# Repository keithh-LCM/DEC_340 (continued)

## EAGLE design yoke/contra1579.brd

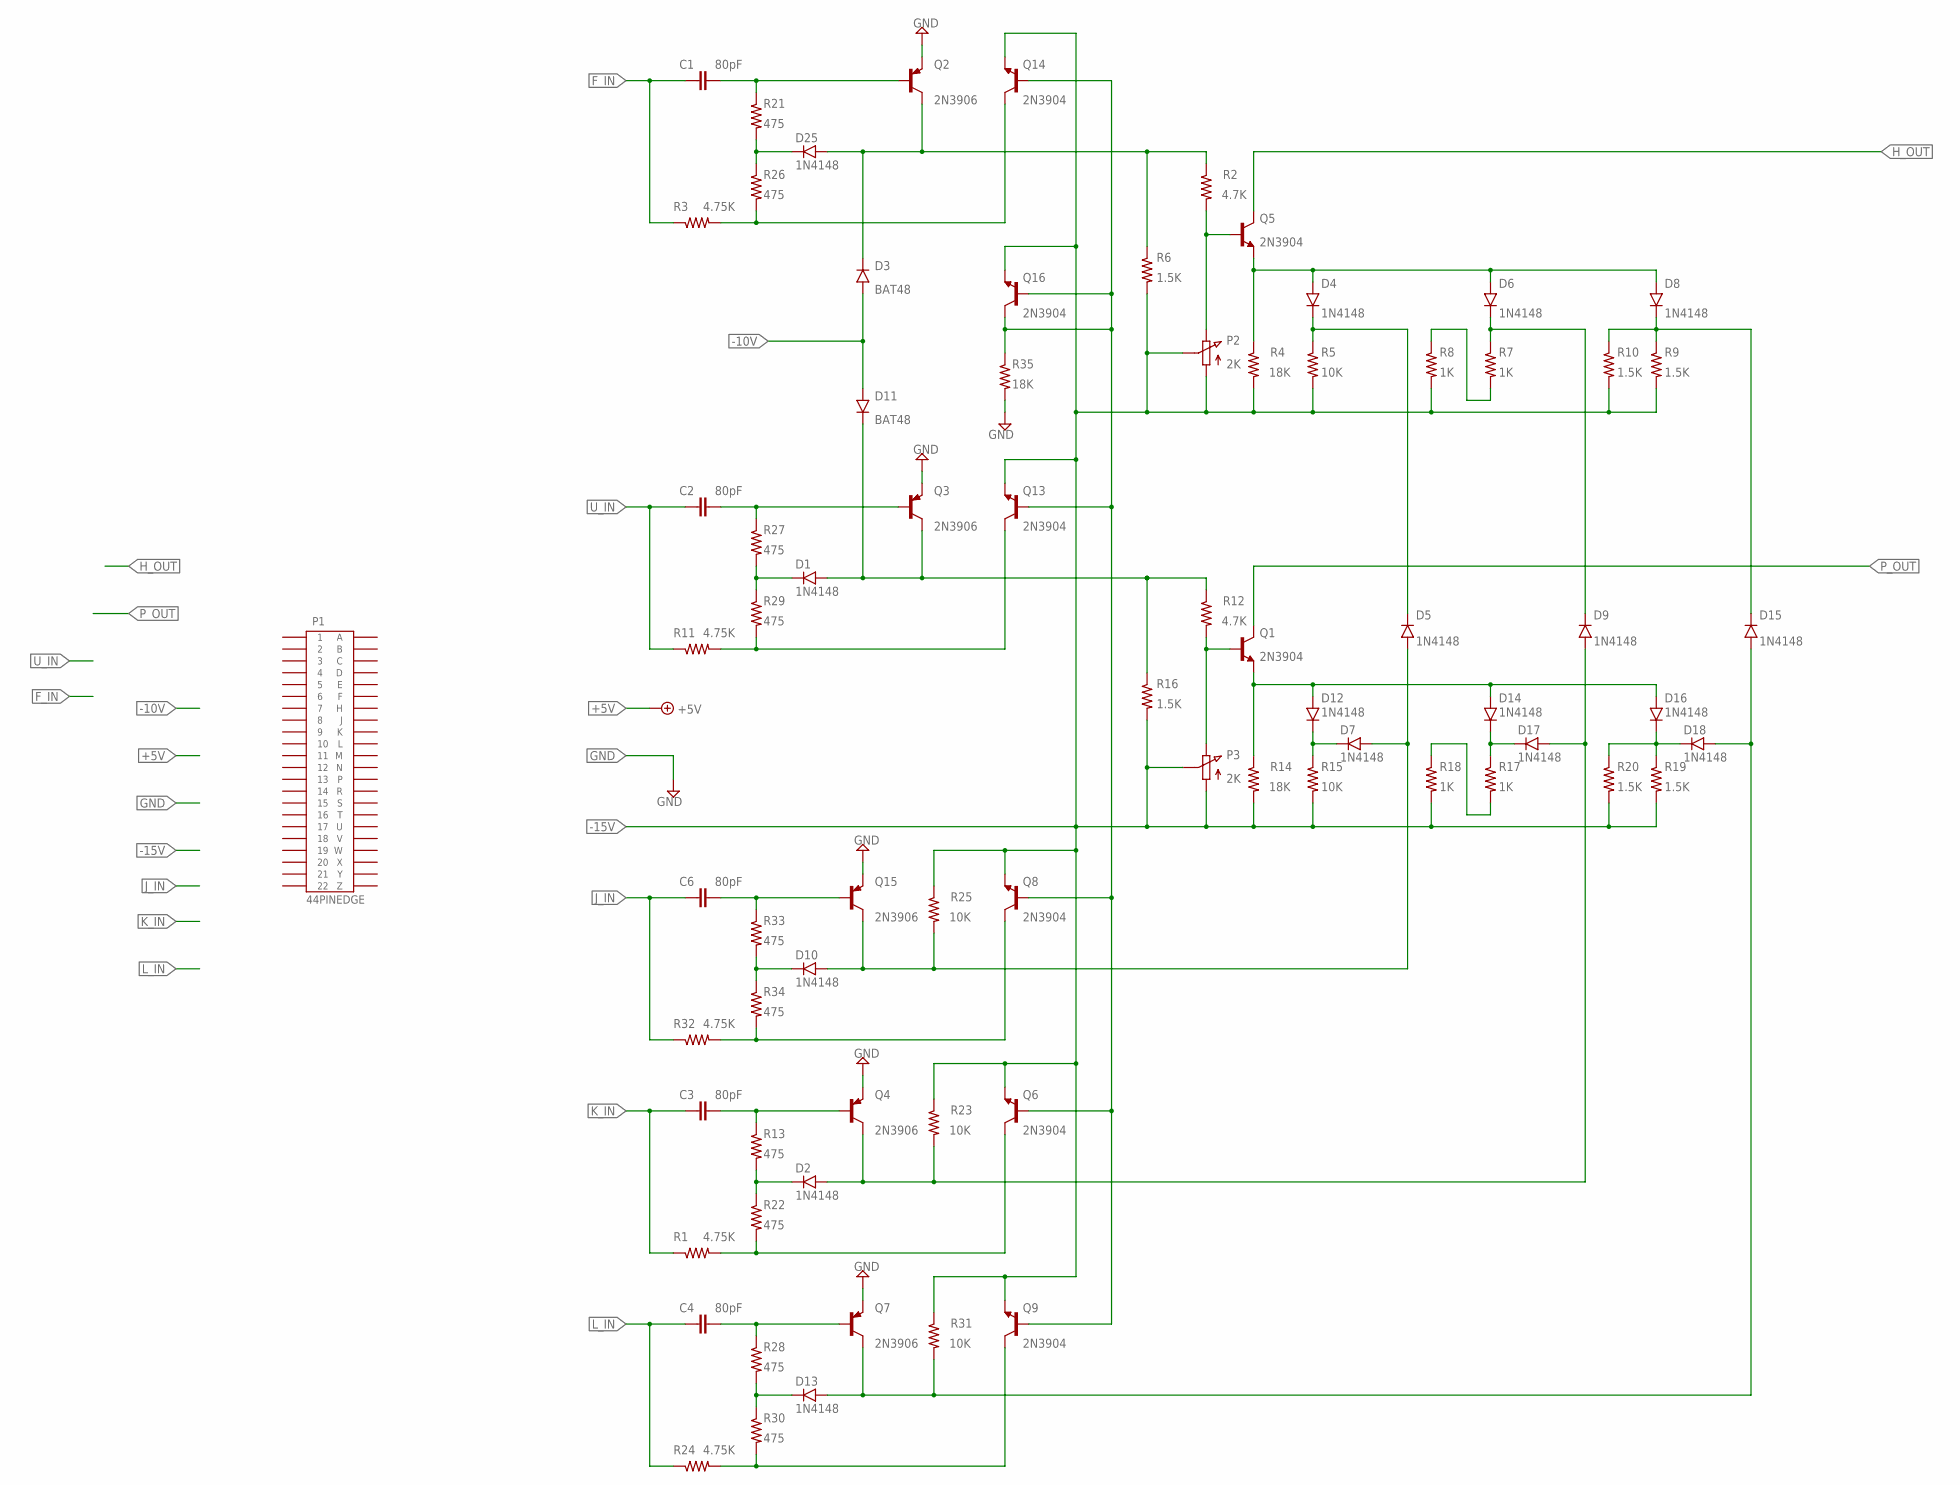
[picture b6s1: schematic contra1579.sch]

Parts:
C1, C2, C3, C4, C6: 80pF; 5MM_TH
D1, D2, D4, D5, D6, D7, D8, D9, D10, D12, D13, D14, D15, D16, D17, D18, D25: 1N4148; DO35-7
D3, D11: BAT48; DO35-7
P1: 44PINEDGE
P2, P3: 2K; 3006P
Q1, Q5, Q6, Q8, Q9, Q13, Q14, Q16: 2N3904; TO92
Q2, Q3, Q4, Q7, Q15: 2N3906; TO92
R1, R3, R11, R24, R32: 4.75K; 0207/10
R2, R12: 4.7K; 0207/10
R4, R14, R35: 18K; 0207/10
R5, R15, R23, R25, R31: 10K; 0207/10
R6, R9, R10, R16, R19, R20: 1.5K; 0207/10
R7, R8, R17, R18: 1K; 0207/10
R13, R21, R22, R26, R27, R28, R29, R30, R33, R34: 475; 0207/10

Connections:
-10V: D3.A, D11.A
-15V: P2.1 (A), P2.2 (S), P3.1 (A), P3.2 (S), Q6.3 (E), Q8.3 (E), Q9.3 (E), Q13.3 (E), Q14.3 (E), Q16.3 (E), R4.2, R5.2, R6.2, R8.2, R9.2, R10.2, R14.2, R15.2, R16.2, R18.2, R19.2, R20.2, R23.1, R25.1, R31.1
F_IN: C1.1, R3.1
GND: Q2.3 (E), Q3.3 (E), Q4.3 (E), Q7.3 (E), Q15.3 (E), R35.2
H_OUT: Q5.1 (C)
J_IN: C6.1, R32.1
K_IN: C3.1, R1.1
L_IN: C4.1, R24.1
unnamed: C1.2, Q2.2 (B), R21.1
unnamed: Q14.1 (C), R3.2, R26.2
unnamed: C3.2, Q4.2 (B), R13.1
unnamed: P2.3 (E), Q5.2 (B), R2.2
unnamed: D4.A, D6.A, D8.A, Q5.3 (E), R4.1
unnamed: D4.C, D5.C, R5.1
unnamed: R7.2, R8.1
unnamed: Q6.1 (C), R1.2, R22.2
unnamed: D25.C, R21.2, R26.1
unnamed: D6.C, D9.C, R7.1
unnamed: D8.C, D15.C, R9.1, R10.1
unnamed: D2.C, R13.2, R22.1
unnamed: C4.2, Q7.2 (B), R28.1
unnamed: C2.2, Q3.2 (B), R27.1
unnamed: Q13.1 (C), R11.2, R29.2
unnamed: P3.3 (E), Q1.2 (B), R12.2
unnamed: D12.A, D14.A, D16.A, Q1.3 (E), R14.1
unnamed: D7.C, D12.C, R15.1
unnamed: D14.C, D17.C, R17.1
unnamed: R17.2, R18.1
unnamed: D16.C, D18.C, R19.1, R20.1
unnamed: Q9.1 (C), R24.2, R30.2
unnamed: D13.C, R28.2, R30.1
unnamed: D1.C, R27.2, R29.1
unnamed: C6.2, Q15.2 (B), R33.1
unnamed: Q8.1 (C), R32.2, R34.2
unnamed: D10.C, R33.2, R34.1
unnamed: Q6.2 (B), Q8.2 (B), Q9.2 (B), Q13.2 (B), Q14.2 (B), Q16.1 (C), Q16.2 (B), R35.1
P_OUT: Q1.1 (C)
U_IN: C2.1, R11.1
VREF: D3.C, D25.A, Q2.1 (C), R2.1, R6.1
VREF1: D2.A, D9.A, D17.A, Q4.1 (C), R23.2
VREF2: D13.A, D15.A, D18.A, Q7.1 (C), R31.2
VREF3: D5.A, D7.A, D10.A, Q15.1 (C), R25.2
VREF5: D1.A, D11.C, Q3.1 (C), R12.1, R16.1

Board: 2 copper layers, 75 parts (0 on the bottom side), 41 nets, no tracks yet.

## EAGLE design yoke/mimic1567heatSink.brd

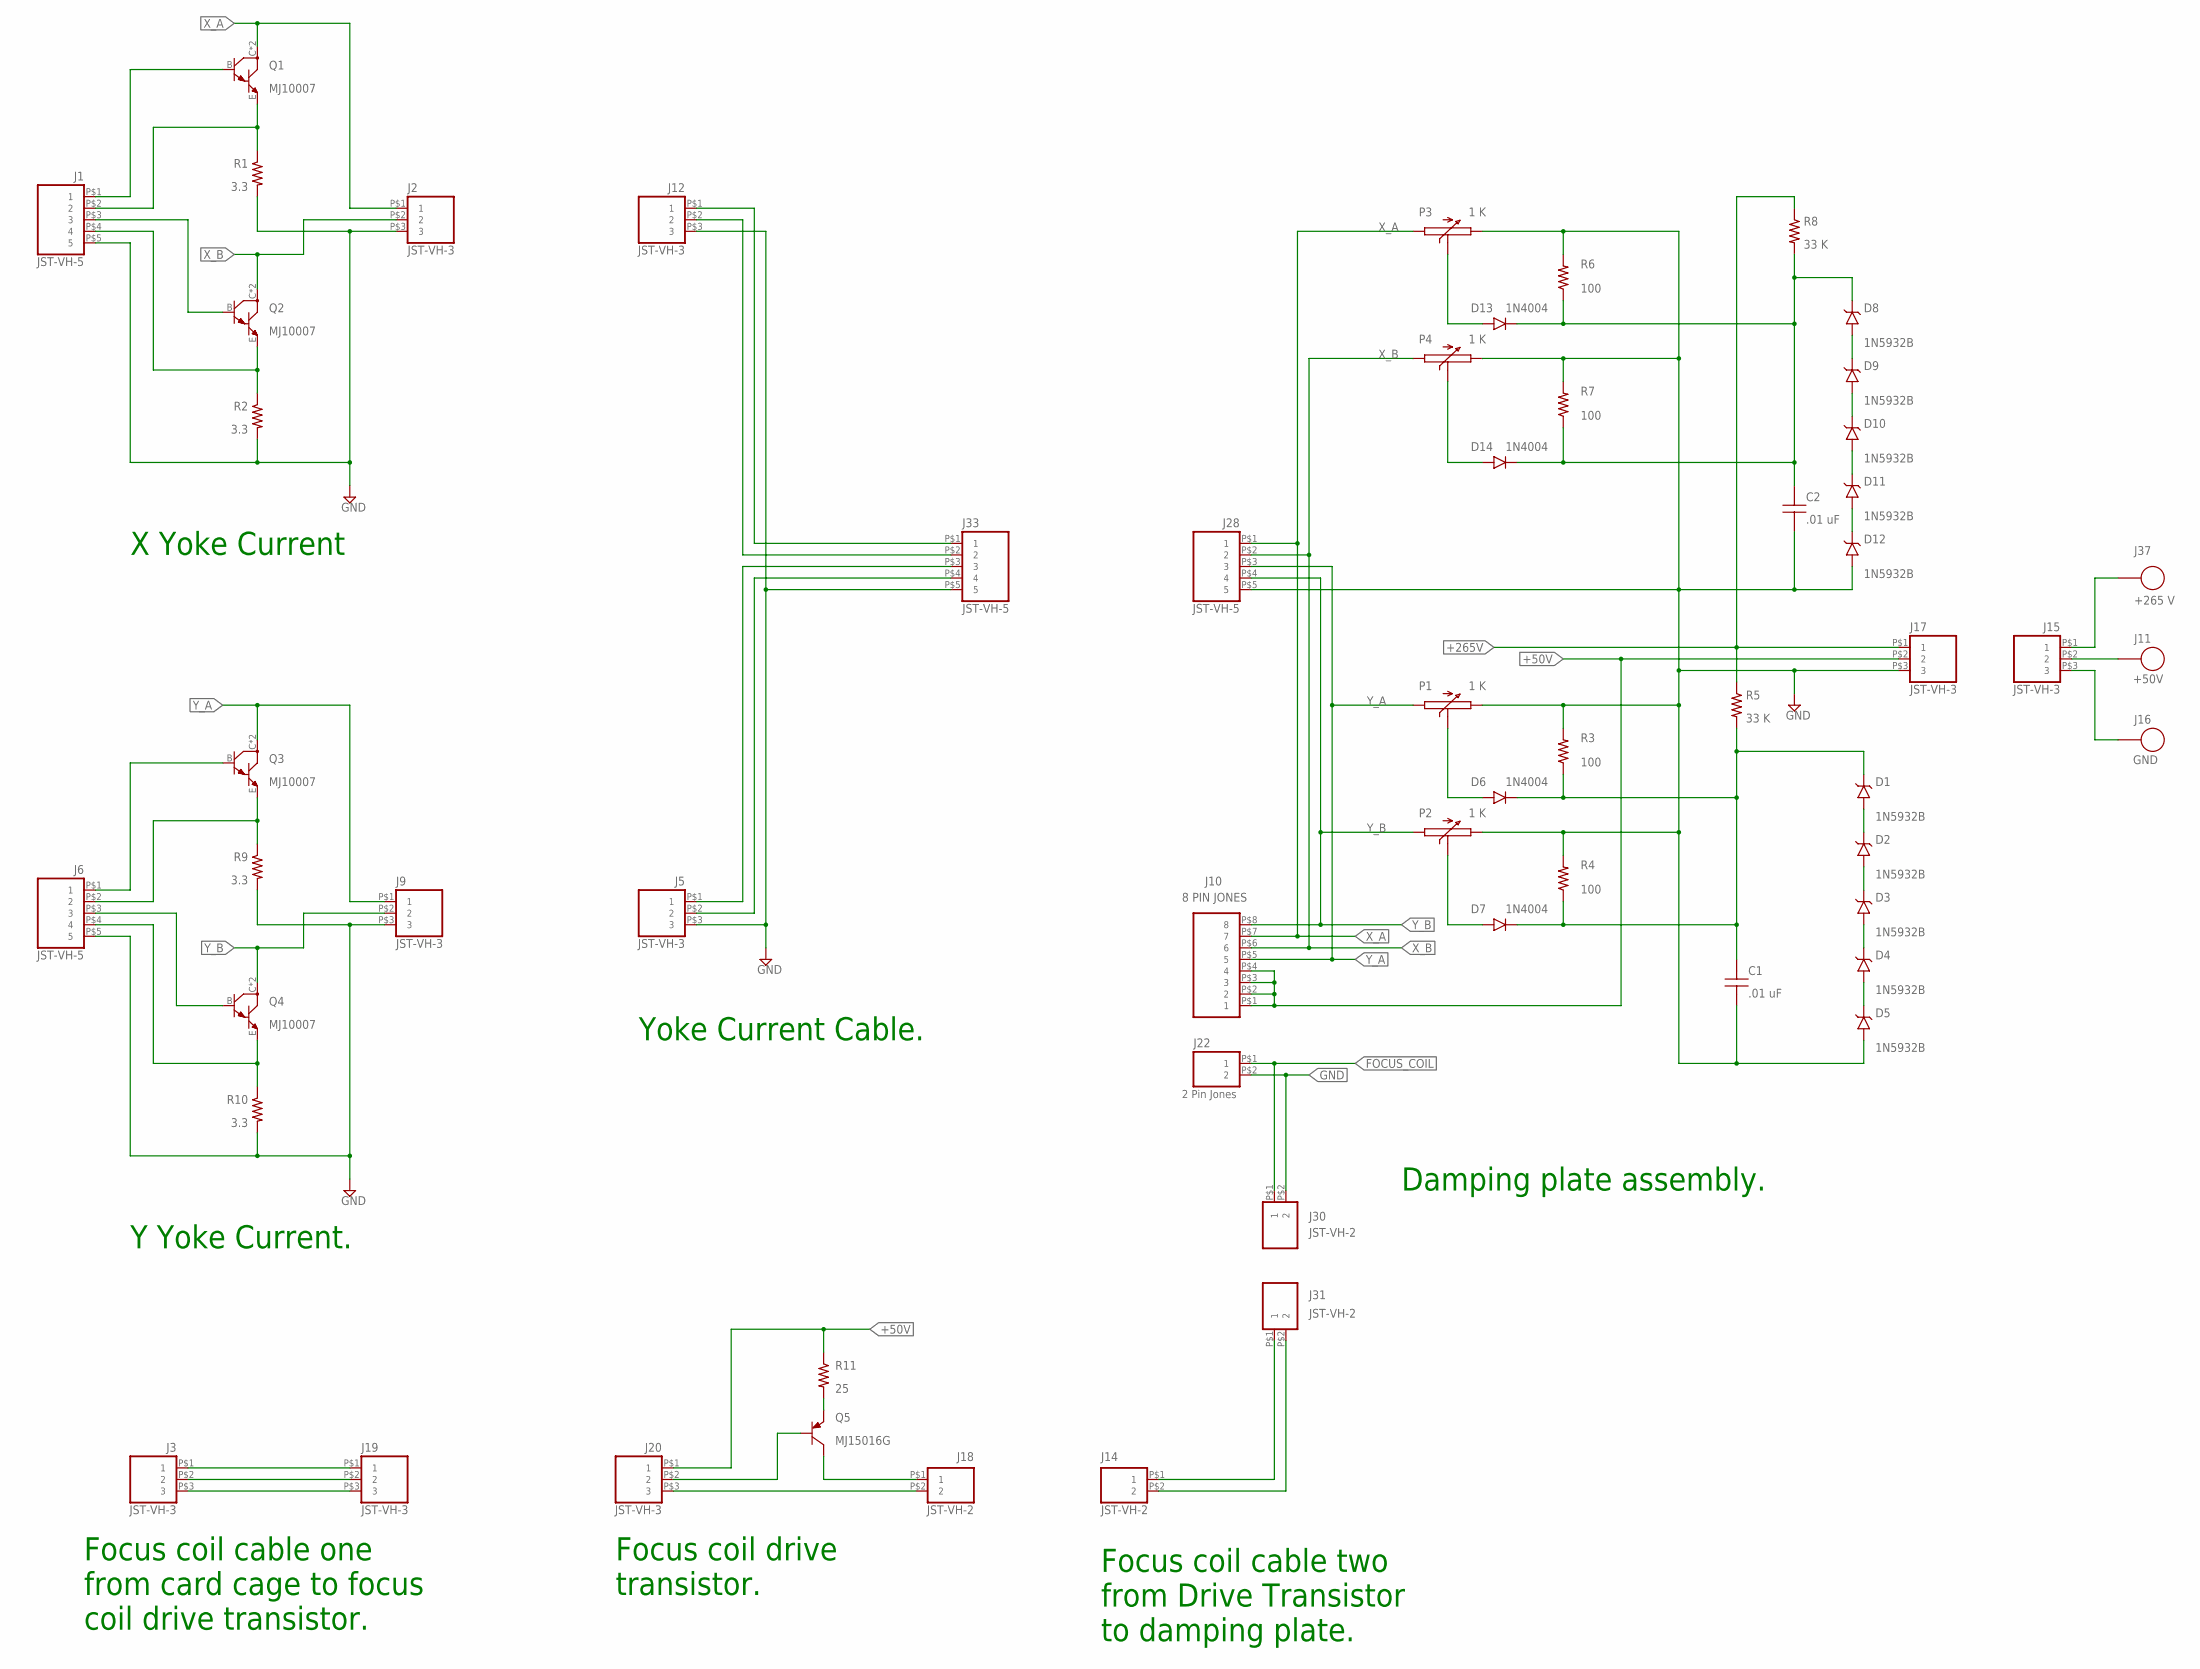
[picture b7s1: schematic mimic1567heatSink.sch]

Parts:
C1, C2: .01 uF; CAP/RADIAL/15MM
D1, D2, D3, D4, D5, D8, D9, D10, D11, D12: 1N5932B; DO41
D6, D7, D13, D14: 1N4004; DO-41-10
J1, J6, J28, J33: JST-VH-5; VHR-5N
J2, J3, J5, J9, J12, J15, J17, J19, J20: JST-VH-3; VHR-3N
J10: 8 PIN JONES; 8PIN_JONES
J11: +50V; AWG18
J14, J18, J30, J31: JST-VH-2; VHR-2N
J16: GND; AWG18
J22: 2 Pin Jones; 2PIN_JONES
J37: +265 V; AWG18
P1, P2, P3, P4: 1 K; 2W_POT
Q1, Q2, Q3, Q4: MJ10007; TO3
Q5: MJ15016G; TO3
R1, R2, R9, R10: 3.3; R_150WATT
R3, R4, R6, R7: 100; 0309/12
R5, R8: 33 K; 2WATT/15
R11: 25; DALE-RH

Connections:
+50V: J10.P$1 (1), J10.P$2 (2), J10.P$3 (3), J10.P$4 (4), J17.P$2 (2), J20.P$1 (1), R11.1
+265V: J17.P$1 (1), R5.1, R8.1
FOCUS_COIL: J18.P$1 (1), J22.P$1 (1), J30.P$1 (1), Q5.C, Q5.C/ (C)
GND: C1.P$2 (2), C2.P$2 (2), D5.A, D12.A, J1.P$5 (5), J2.P$3 (3), J5.P$3 (3), J6.P$5 (5), J9.P$3 (3), J12.P$3 (3), J17.P$3 (3), J18.P$2 (2), J20.P$3 (3), J22.P$2 (2), J28.P$5 (5), J30.P$2 (2), J33.P$5 (5), P1.E (3), P2.E (3), P3.E (3), P4.E (3), R1.P$2, R2.P$2, R3.2, R4.2, R6.2, R7.2, R9.P$2, R10.P$2
unnamed: J20.P$2 (2), Q5.B
unnamed: J1.P$1 (1), Q1.B
unnamed: J1.P$2 (2), Q1.E, R1.P$1
unnamed: Q5.E, R11.2
unnamed: J1.P$4 (4), Q2.E, R2.P$1
unnamed: J1.P$3 (3), Q2.B
unnamed: J3.P$3 (3), J19.P$3 (3)
unnamed: J3.P$2 (2), J19.P$2 (2)
unnamed: D1.A, D2.C
unnamed: D2.A, D3.C
unnamed: D3.A, D4.C
unnamed: D4.A, D5.C
unnamed: J15.P$1 (1), J37.P$1
unnamed: C1.P$1 (1), D1.C, D6.C, D7.C, R3.1, R4.1, R5.2
unnamed: D6.A, P1.S (2)
unnamed: J11.P$1, J15.P$2 (2)
unnamed: J15.P$3 (3), J16.P$1
unnamed: D8.A, D9.C
unnamed: D7.A, P2.S (2)
unnamed: J6.P$3 (3), Q4.B
unnamed: D9.A, D10.C
unnamed: D10.A, D11.C
unnamed: D11.A, D12.C
unnamed: J14.P$2 (2), J31.P$2 (2)
unnamed: J3.P$1 (1), J19.P$1 (1)
unnamed: J6.P$1 (1), Q3.B
unnamed: C2.P$1 (1), D8.C, D13.C, D14.C, R6.1, R7.1, R8.2
unnamed: J6.P$2 (2), Q3.E, R9.P$1
unnamed: D13.A, P3.S (2)
unnamed: J14.P$1 (1), J31.P$1 (1)
unnamed: D14.A, P4.S (2)
unnamed: J6.P$4 (4), Q4.E, R10.P$1
X_A: J2.P$1 (1), J10.P$7 (7), J12.P$1 (1), J28.P$1 (1), J33.P$1 (1), P3.A (1), Q1.C, Q1.C/ (C)
X_B: J2.P$2 (2), J10.P$6 (6), J12.P$2 (2), J28.P$2 (2), J33.P$2 (2), P4.A (1), Q2.C, Q2.C/ (C)
Y_A: J5.P$1 (1), J9.P$1 (1), J10.P$5 (5), J28.P$3 (3), J33.P$3 (3), P1.A (1), Q3.C, Q3.C/ (C)
Y_B: J5.P$2 (2), J9.P$2 (2), J10.P$8 (8), J28.P$4 (4), J33.P$4 (4), P2.A (1), Q4.C, Q4.C/ (C)

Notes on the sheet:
Damping plate assembly.
Focus coil cable two from Drive Transistor to damping plate.
Yoke Current Cable.
Focus coil cable one from card cage to focus coil drive transistor.
Focus coil drive transistor.
X Yoke Current
Y Yoke Current.

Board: 2 copper layers, 58 parts (0 on the bottom side), 40 nets, no tracks yet.

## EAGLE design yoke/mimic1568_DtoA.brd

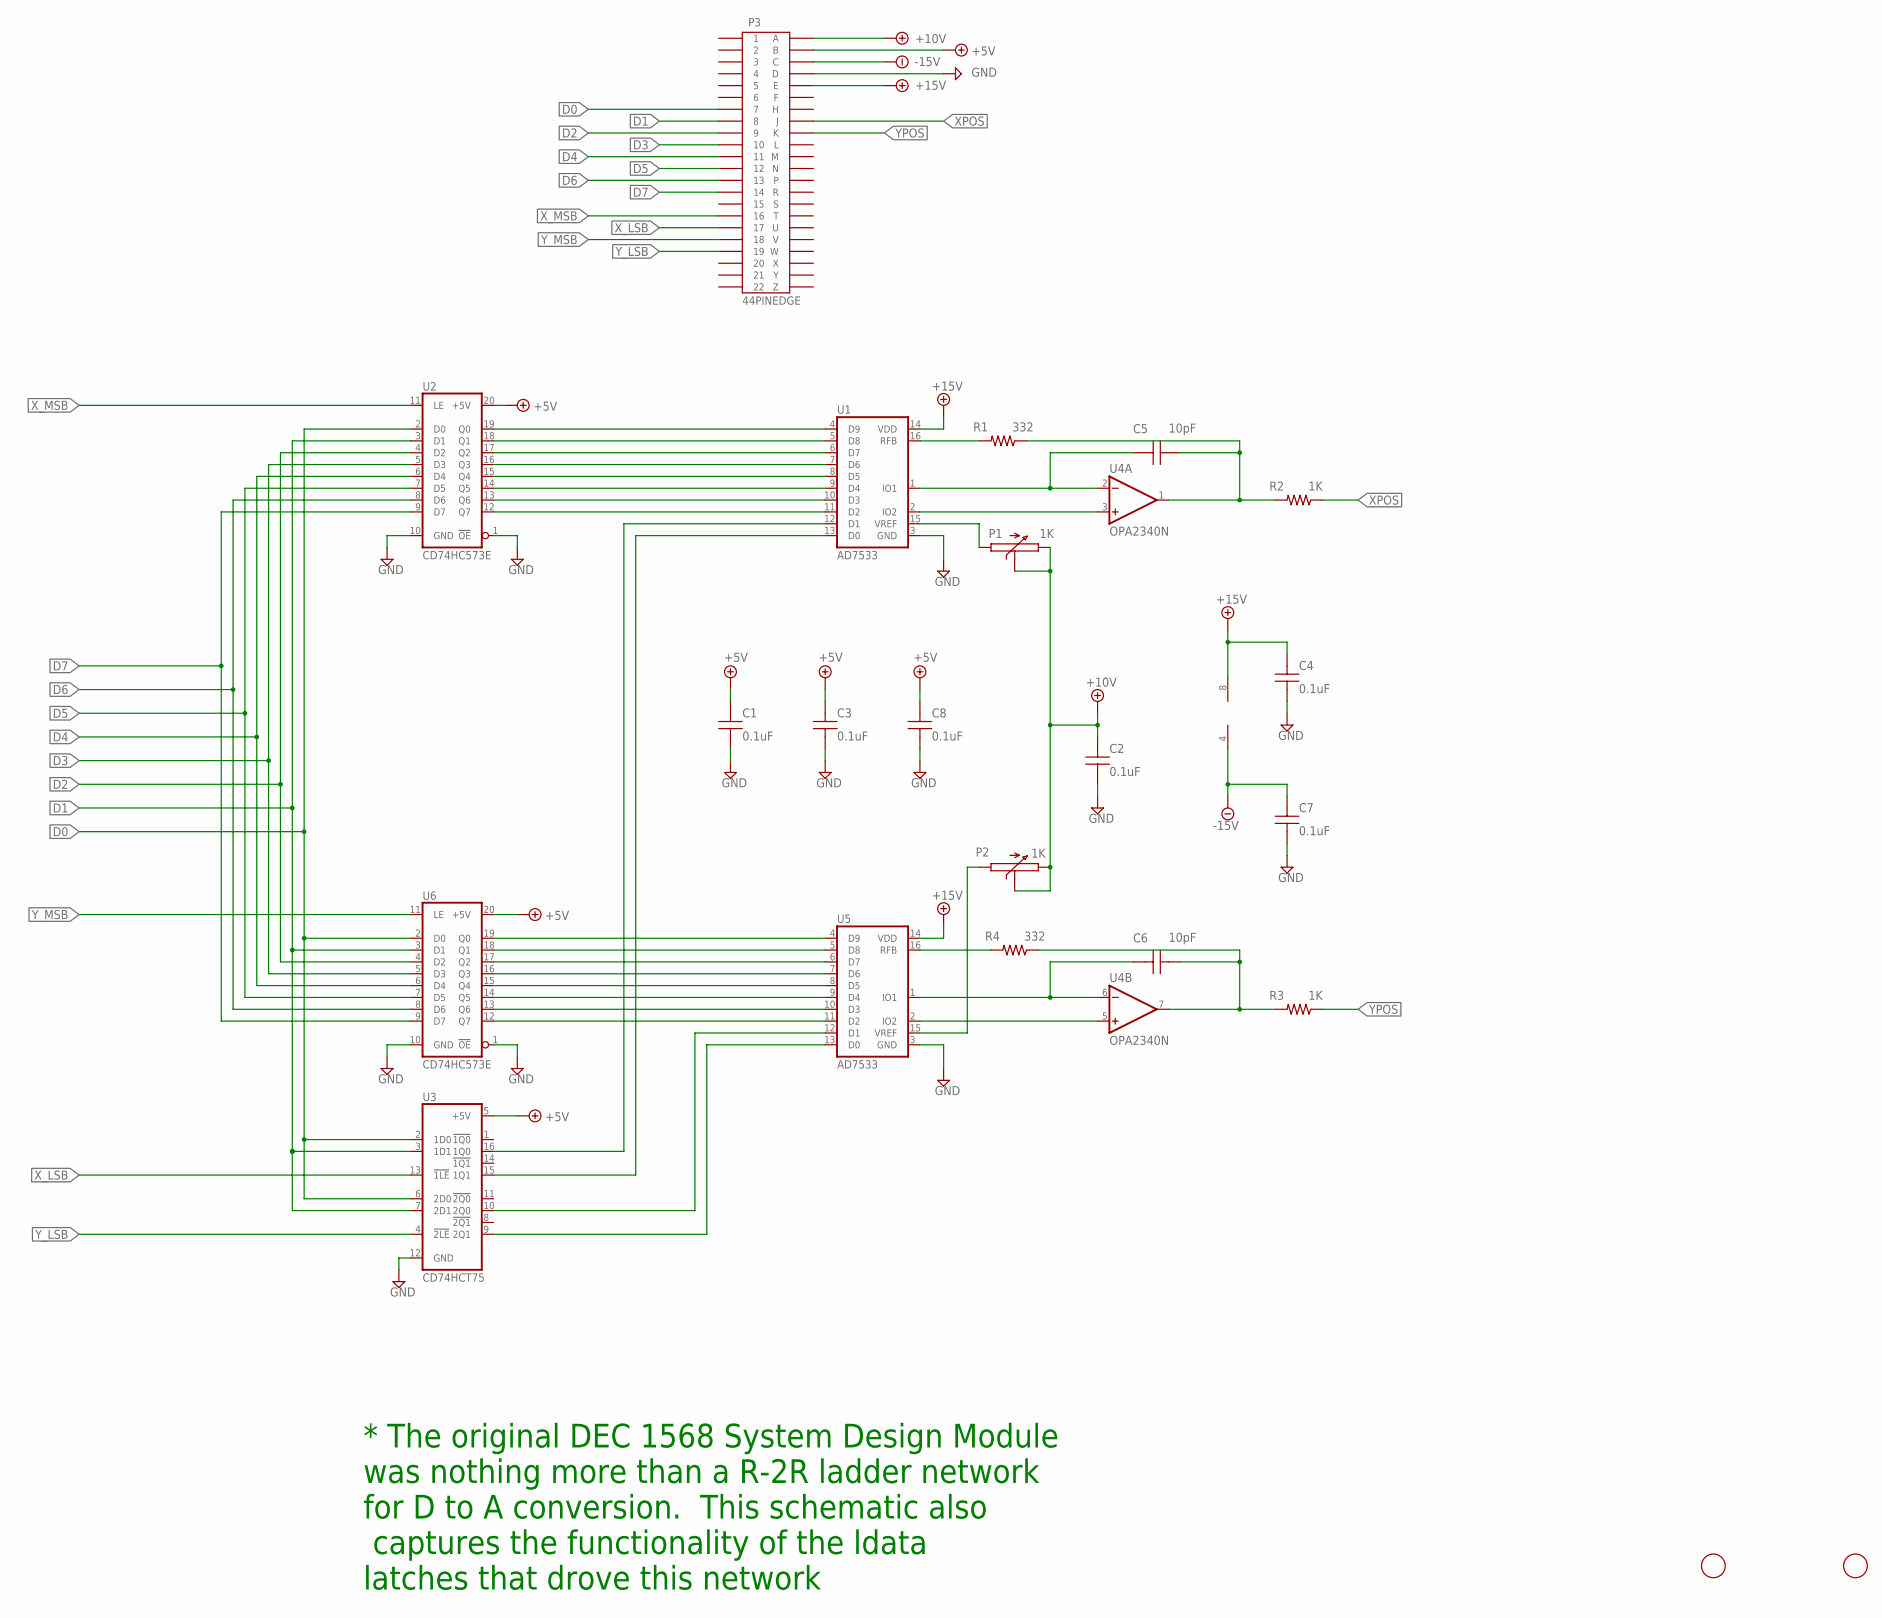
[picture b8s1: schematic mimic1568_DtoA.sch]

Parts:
C1, C2, C3, C4, C7, C8: 0.1uF; 5MM_TH
C5, C6: 10pF; 5MM_TH
P1, P2: 1K; 3006P
P3: 44PINEDGE
R1, R4: 332; 0207/10
R2, R3: 1K; 0207/10
U1, U5: AD7533; DIP-16
U2, U6: CD74HC573E; DIP-20
U3: CD74HCT75; DIP-16
U4: OPA2340N; DIP-08
U$1, U$2: FIDUCIAL; FIDUCIAL_1MM

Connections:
+5V: C1.1, C3.1, C8.1, P3.B, U2.20 (+5V), U3.5 (+5V), U6.20 (+5V)
+10V: C2.1, P1.2, P1.3, P2.2, P2.3, P3.A
+15V: C4.1, P3.E, U1.14 (VDD), U4.8 (V+), U5.14 (VDD)
-15V: C7.1, P3.C, U4.4 (V-)
D0: P3.7, U2.2 (D0), U3.2 (1D0), U3.6 (2D0), U6.2 (D0)
D1: P3.8, U2.3 (D1), U3.3 (1D1), U3.7 (2D1), U6.3 (D1)
D2: P3.9, U2.4 (D2), U6.4 (D2)
D3: P3.10, U2.5 (D3), U6.5 (D3)
D4: P3.11, U2.6 (D4), U6.6 (D4)
D5: P3.12, U2.7 (D5), U6.7 (D5)
D6: P3.13, U2.8 (D6), U6.8 (D6)
D7: P3.14, U2.9 (D7), U6.9 (D7)
GND: C1.2, C2.2, C3.2, C4.2, C7.2, C8.2, P3.D, U1.3 (GND), U2.1 (!OE), U2.10 (GND), U3.12 (GND), U5.3 (GND), U6.1 (!OE), U6.10 (GND)
unnamed: U3.9 (2Q1), U5.13 (D0)
unnamed: R4.2, U5.16 (RFB)
unnamed: U1.12 (D1), U3.16 (1Q0)
unnamed: U1.13 (D0), U3.15 (1Q1)
unnamed: C5.1, U1.1 (IO1), U4.2 (-IN)
unnamed: U1.2 (IO2), U4.3 (+IN)
unnamed: U5.4 (D9), U6.19 (Q0)
unnamed: U5.5 (D8), U6.18 (Q1)
unnamed: U5.6 (D7), U6.17 (Q2)
unnamed: U5.7 (D6), U6.16 (Q3)
unnamed: U5.8 (D5), U6.15 (Q4)
unnamed: U5.9 (D4), U6.14 (Q5)
unnamed: U5.10 (D3), U6.13 (Q6)
unnamed: U5.11 (D2), U6.12 (Q7)
unnamed: C5.2, R1.1, R2.2, U4.1 (OUT)
unnamed: P1.1, U1.15 (VREF)
unnamed: U1.4 (D9), U2.19 (Q0)
unnamed: U1.5 (D8), U2.18 (Q1)
unnamed: U1.6 (D7), U2.17 (Q2)
unnamed: U1.7 (D6), U2.16 (Q3)
unnamed: U1.8 (D5), U2.15 (Q4)
unnamed: U1.9 (D4), U2.14 (Q5)
unnamed: U1.10 (D3), U2.13 (Q6)
unnamed: U1.11 (D2), U2.12 (Q7)
unnamed: U3.10 (2Q0), U5.12 (D1)
unnamed: R1.2, U1.16 (RFB)
unnamed: C6.2, R3.2, R4.1, U4.7 (OUT)
unnamed: C6.1, U4.6 (-IN), U5.1 (IO1)
unnamed: U4.5 (+IN), U5.2 (IO2)
unnamed: P2.1, U5.15 (VREF)
XPOS: P3.J, R2.1
X_LSB: P3.17, U3.13 (!1LE)
X_MSB: P3.16, U2.11 (LE)
YPOS: P3.K, R3.1
Y_LSB: P3.19, U3.4 (!2LE)
Y_MSB: P3.18, U6.11 (LE)

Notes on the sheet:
* The original DEC 1568 System Design Module was nothing more than a R-2R ladder network for D to A conversion. This schematic also captures the functionality of the ldata latches that drove this network

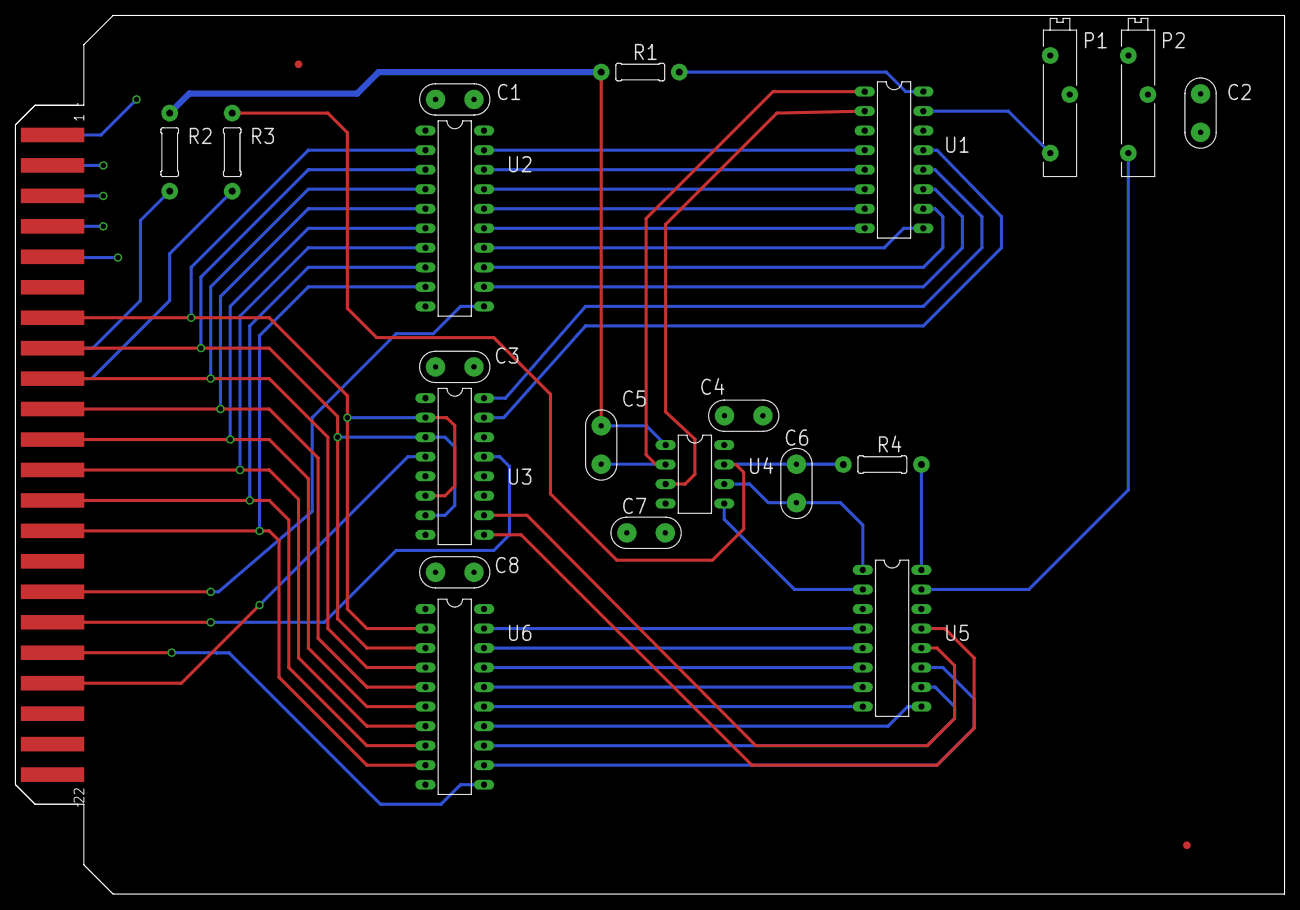
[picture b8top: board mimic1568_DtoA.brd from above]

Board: 4 copper layers, 165.1 x 114.3 mm, 23 parts (0 on the bottom side), 49 nets.
